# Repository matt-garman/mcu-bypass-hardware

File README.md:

<!-- SPDX-License-Identifier: CERN-OHL-P-2.0 -->

# MCU Hardware for Switch Debounce and Electric Instrument Effects Switching

## Overview

This is the companion repo to [mcu-bypass-firmware](https://github.com/matt-garman/mcu-bypass-firmware).

These hardware designs are intended to be used for electric
instrument effects (e.g. guitar effect pedals) bypass switching.
Many of these schemes rely on a microcontroller to act as the
"brains" of the switching scheme; see the other repo for MCU
firmware.

## License

Copyright (c) 2026 Matthew Garman

These hardware designs (schematics, PCB layouts, fabrication files,
documentation, and supporting scripts) are licensed under the
[CERN Open Hardware Licence Version 2 - Permissive](LICENSE)
(SPDX: `CERN-OHL-P-2.0`). The companion firmware is licensed separately
under the MIT License; see that repo for details.

In short, you may use, modify, and share these designs, and make and
sell products based on them, including commercial products. The main
condition is keeping the copyright and license notices available to
whoever receives the design files or a product built from them. The
designs are provided as-is, WITHOUT ANY WARRANTY; see the
[license](LICENSE) for the actual terms.

## Credit (appreciated, not required)

If you use these designs or the firmware in something you build, and
especially in something you sell, a shout-out would be much appreciated.
A line in your manual, product page, or "About" screen is perfect.
For example:

> Bypass switching based on [mcu-bypass-hardware](https://github.com/matt-garman/mcu-bypass-hardware)
> and [mcu-bypass-firmware](https://github.com/matt-garman/mcu-bypass-firmware)
> by Matt Garman.

You have my permission to use my name this way to credit these
projects. Please don't word it in a way that suggests I endorse, or
was involved with, your product.

## Projects

  - [projects/attiny13a-buffered-electrical-bypass-quasi-ic](projects/attiny13a-buffered-electrical-bypass-quasi-ic/)
  - [projects/attiny202-buffered-electrical-bypass-quasi-ic](projects/attiny202-buffered-electrical-bypass-quasi-ic/)
  - [projects/attiny13a-relay-bypass-quasi-ic](projects/attiny13a-relay-bypass-quasi-ic)

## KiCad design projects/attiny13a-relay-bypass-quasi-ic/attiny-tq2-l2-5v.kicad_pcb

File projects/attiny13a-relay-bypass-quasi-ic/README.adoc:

// SPDX-License-Identifier: CERN-OHL-P-2.0

= ATtiny13A Relay Bypass Module and Quasi-IC

== Overview

The design and intent of this module is broadly similar to that of
its sister projects,
link:../attiny13a-buffered-electrical-bypass-quasi-ic/[attiny13a-buffered-electrical-bypass-quasi-ic]
and
link:../attiny202-buffered-electrical-bypass-quasi-ic/[attiny202-buffered-electrical-bypass-quasi-ic].
Briefly, this
module is intended to offer the same "plug and play" convenience of
an integrated circuit, one that offers analog signal
switching, as well as engage/bypass state management
and status LED lighting/darking.

This module's key differences are:

  * This project uses through-hole components, and is therefore
    physically larger
  * While the project has "ATtiny13A" in the name, it actually uses
    any of three microcontrollers from the the "AVR Classic" family;
    specifically, firmware exists for ATtiny13A, ATtiny45, and
    ATtiny85 (the firmware is identical for all MCUs, except in
    necessary hardware-specific details)
  * Like the ATtiny13A-based Quasi-IC, this PCB uses a single row of
    pin headers; in fact the two modules are designed to be
    interchangeable
  * This module contains no buffers
  * This module uses a mechanical relay (Panasonic TQ-L2-5V) for
    true bypass switching
  * This module has additional I/O for use as a standalone module
    with commercial/off-the-shelf (COTS) PCBs (e.g. link:https://www.pedalpcb.com/[PedalPCB] 
    or link:https://www.aionfx.com/[AionFX] 
  * This is a "belt-and-suspenders" design (see below) that
    decouples the MCU from the relay coil via MOSFETs and protection
    diodes; thus, it can be easily adapted for use with other MCUs

== Design Notes

This is deliberately a "belt-and-suspenders" design.  That is, some
may argue that the design is over-engineered with some extraneous
parts.  Specifically: the use of the relay coil flyback protection
diodes (D1, D3), and the coil-current-sinking MOSFETs (Q1, Q3).  In
similar designs, the AVR MCU directly drives the relay coil,
removing the need for the protection diodes and current-sinking
transistors.  The AVR Classic MCU GPIO pins have built-in protection
diodes _and_ are rated to source/sink the relay coil current.
Similarly, it is also possible for the MCU to directly drive the
status LED.

Using the MOSFETs and protection diodes to isolate the relay coil
from the MCU provides additional safety for the MCU, though at the
expense of added PCB footpring and BOM cost.  Additionally, it makes
the design trivially adaptable to other microcontrollers which may
not have GPIO pins that are as rugged as the AVR Classic.  (MOSFET
gates present virtually zero load, so can be trivially activated by
practically any logic chip.)

_Presumably_, cheaper NPN BJT transistors (such as 2n3904) can be
used in place of the 2n7000 N-Channel MOSFETs.  *But this is
untested*.

While generally we refer to the TQ-L2-5V part for the relay, the
*TQ-L2-4.5V* is arguably the ideal part.  There is a voltage drop of
approximately 0.7V across the MOSFETs when they are switched on.
Therefore, the actual voltage presented to the relay coils is
approximately 4.3V, rather than 5V.  Thus, the "4.5V" part is a
better fit.  However, in practice, the 4.5V part is less common and
generally more expensive.  Given that the operating margins of the
TQ2 parts are fairly generous, the 5V part still has sufficient
margin in this design and works reliably.  Choose the 4.5V part only
if it's available and the cost is the same as the 5V part.

== Schematic

link:attiny-tq2-l2-5v.pdf[Downloadable PDF]

image::attiny-tq2-l2-5v.svg[opts=inline]

== Module Pinout

This module has a total of 15 pins with 2.54mm pitch.  There is
essentially three groups of pin headers.  The overall numbering, as
viewed from the component side, is somewhat awkward: 10, 11, 1, 2,
3, 4, 5, 6, 7, 8, 9, 12, 13, 14, 15.

The awkward numbering is so that the middle group of pins, i.e. 1
through 9, are compatible with the other quasi-IC modules that only
have these pins.

The other two groups of pins (10,11) and (12,13,14,15) allow the
module to be used generically with COTS PCBs.

....
 10| 11     1 | 2 | 3 | 4 | 5 | 6 | 7 | 8 | 9      12| 13| 14| 15
GND|VDC    +9V|GND|JIN|SND|LSW|RET|JOU|GND|FSW    GND|GND|LSW|+5V
....

[cols="1,2,6",options="header"]
|===
| Pin | Signal | Description

| 10, 2, 8, 12, 13
| GND
| Ground (0-volt)

| 11
| VDC
| Post-reverse polarity projection supply voltage; this is the
voltage that is created from the +9V pin, _after_ D2 and R13; this
can be used to power an effect PCB, particularly for many from AionFX 

| 1
| +9V
| Supply input; the module has a reverse-polarity shunt diode (D2)
and a 100-ohm series resistor (R13) on this pin

| 3
| JIN
| Signal input, from the input jack; routed directly to the relay

| 4
| SND
| Signal to the effect circuit's input, either JIN or GND; switched
by the relay

| 5, 14
| LSW
| Status LED cathode, switched to ground by Q3 through CLR1 (a
current-limiting resistor)

| 6
| RET
| The effect circuit's output, returning to the module; routed
directly to the relay

| 7
| JACK_OUT
| Signal output, either JIN or RET; routed directly to and switched
by the relay

| 9
| FSW
| One pin of a two-pin momentary, normally-open footswitch; the
pull-up and RC filter are on the module (the footswitch's other pin
is tied to GND)

| 15
| +5V
| The +5V supply used by the AVR MCU and the relay itself; this pin,
along with the LSW pin, can be used for the status LED (note that
generally a smaller current-limiting resistor can be used with 5V
versus 9V)
|===

// TODO: supply voltage range and typical current draw.

== Modifying

The KiCad project is
link:attiny-tq2-l2-5v.kicad_pro[attiny-tq2-l2-5v.kicad_pro],
in this directory.  KiCad version 10.0.5 was used.

== Fabrication and Assembly

The following files are offered for fabrication.  Caveats,
disclaimers and warnings:

  * I used these with link:JLCPCB[https://www.jlcpcb.com]; their
    suitability for other fabricators is unknown
  * They were generated from the KiCad project via
    link:kicad-jlcpcb-tools[https://github.com/bouni/kicad-jlcpcb-tools]

The files:

  * link:GERBER-attiny-tq2-l2-5v.zip[GERBER-attiny-tq2-l2-5v.zip]:
    Gerber files
  * link:attiny-tq2-l2-5v.BOM.csv[attiny-tq2-l2-5v.BOM.csv]: BOM (CSV format)
  * link:attiny-tq2-l2-5v.BOM.pdf[attiny-tq2-l2-5v.BOM.pdf]: BOM (PDF format)

== Build Reports

  * link:https://forum.pedalpcb.com/threads/pez-rojo-custom-menatone-red-snapper.30439/[Pez Rojo]
    (originally used the ATtiny202 quasi-IC, but later changed to this module)

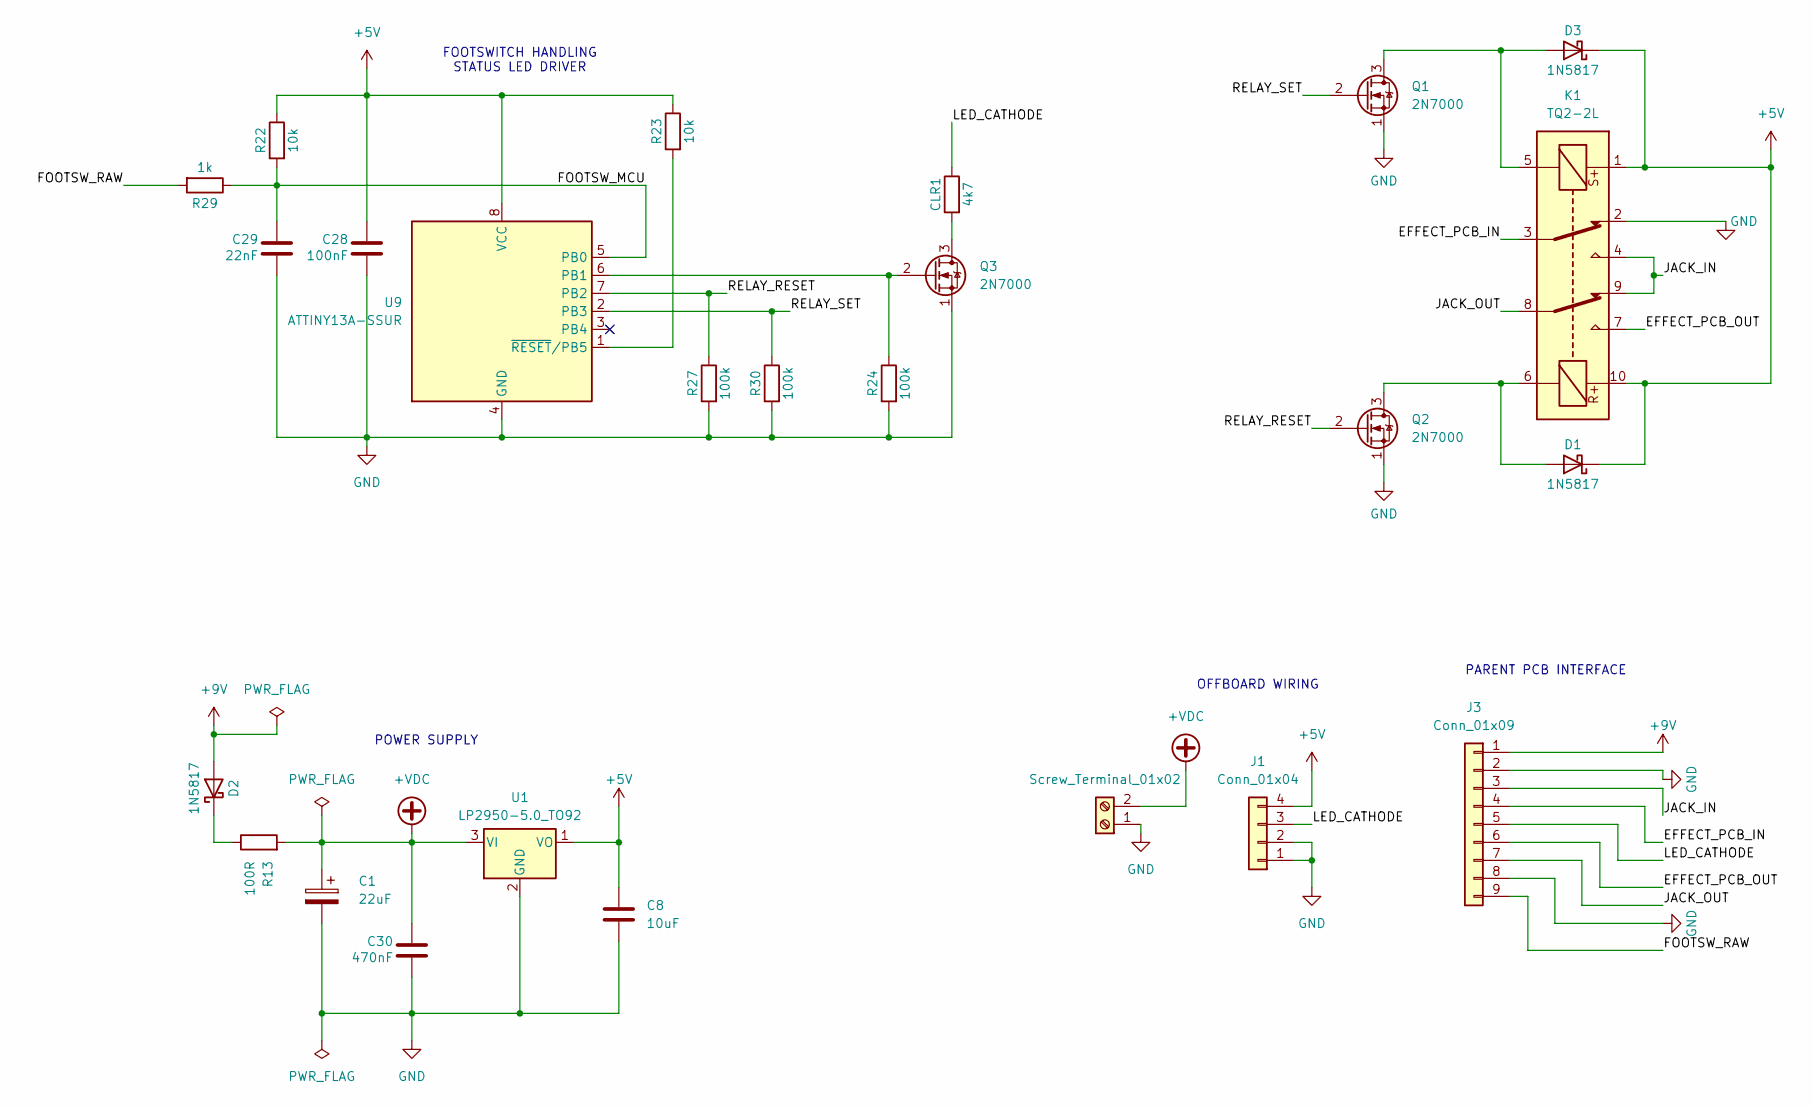
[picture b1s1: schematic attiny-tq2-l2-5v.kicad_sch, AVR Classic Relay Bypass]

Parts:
C1: 22uF; CP_Radial_D5.0mm_P2.50mm
C8: 10uF; C_Rect_L7.2mm_W2.5mm_P5.00mm_FKS2_FKP2_MKS2_MKP2; LCSC C13585
C28: 100nF; C_Rect_L7.2mm_W2.5mm_P5.00mm_FKS2_FKP2_MKS2_MKP2; LCSC C14663
C29: 22nF; C_Rect_L7.2mm_W2.5mm_P5.00mm_FKS2_FKP2_MKS2_MKP2; LCSC C21122
C30: 470nF; C_Rect_L7.2mm_W2.5mm_P5.00mm_FKS2_FKP2_MKS2_MKP2; LCSC C14663
CLR1: 4k7; R_Axial_DIN0204_L3.6mm_D1.6mm_P5.08mm_Horizontal; LCSC C23162
D1, D2, D3: 1N5817; D_DO-35_SOD27_P7.62mm_Horizontal
J1: Conn_01x04; OffboardWireHoles_1x04_P2.54mm
J3: Conn_01x09; OffboardWireHoles_1x09_P2.54mm
J8: Screw_Terminal_01x02; OffboardWireHoles_1x02_P2.54mm
K1: TQ2-2L; Relay_DPDT_A-4.5W-K
Q1, Q2, Q3: 2N7000; TO-92_Inline_Wide
R13: 100R; R_Axial_DIN0204_L3.6mm_D1.6mm_P5.08mm_Horizontal
R22: 10k; R_Axial_DIN0204_L3.6mm_D1.6mm_P5.08mm_Horizontal
R23: 10k; R_Axial_DIN0204_L3.6mm_D1.6mm_P5.08mm_Horizontal; LCSC C25804
R24, R27, R30: 100k; R_Axial_DIN0204_L3.6mm_D1.6mm_P5.08mm_Horizontal; LCSC C25803
R29: 1k; R_Axial_DIN0204_L3.6mm_D1.6mm_P5.08mm_Horizontal; LCSC C21190
U1: LP2950-5.0_TO92; TO-92_Inline_Wide
U9: ATTINY13A-SSUR; DIP-8_W7.62mm; LCSC C40382

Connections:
+5V: C8.2, C28.2, D1.1 (K), D3.1 (K), J1.4, K1.1, K1.10, R22.1, R23.1, U1.1 (VO), U9.8 (VCC)
+9V: D2.2 (A), J3.1
+VDC: C1.1, C30.2, J8.2, R13.2, U1.3 (VI)
/EFFECT_PCB_IN: J3.4, K1.3
/EFFECT_PCB_OUT: J3.6, K1.7
/FOOTSW_MCU: C29.2, R22.2, R29.1, U9.5 (PB0)
/FOOTSW_RAW: J3.9, R29.2
/JACK_IN: J3.3, K1.4, K1.9
/JACK_OUT: J3.7, K1.8
/LED_CATHODE: CLR1.1, J1.3, J3.5
/RELAY_RESET: Q2.2 (G), R27.1, U9.7 (PB2)
/RELAY_SET: Q1.2 (G), R30.1, U9.2 (PB3)
GND: C1.2, C8.1, C28.1, C29.1, C30.1, J1.1, J1.2, J3.2, J3.8, J8.1, K1.2, Q1.1 (S), Q2.1 (S), Q3.1 (S), R24.2, R27.2, R30.2, U1.2 (GND), U9.4 (GND)
unnamed: D1.2 (A), K1.6, Q2.3 (D)
unnamed: D2.1 (K), R13.1
unnamed: D3.2 (A), K1.5, Q1.3 (D)
unnamed: CLR1.2, Q3.3 (D)
unnamed: Q3.2 (G), R24.1, U9.6 (PB1)
unnamed: R23.2, U9.1 (~RESET/PB5)

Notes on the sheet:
PARENT PCB INTERFACE
FOOTSWITCH HANDLING STATUS LED DRIVER
OFFBOARD WIRING
POWER SUPPLY

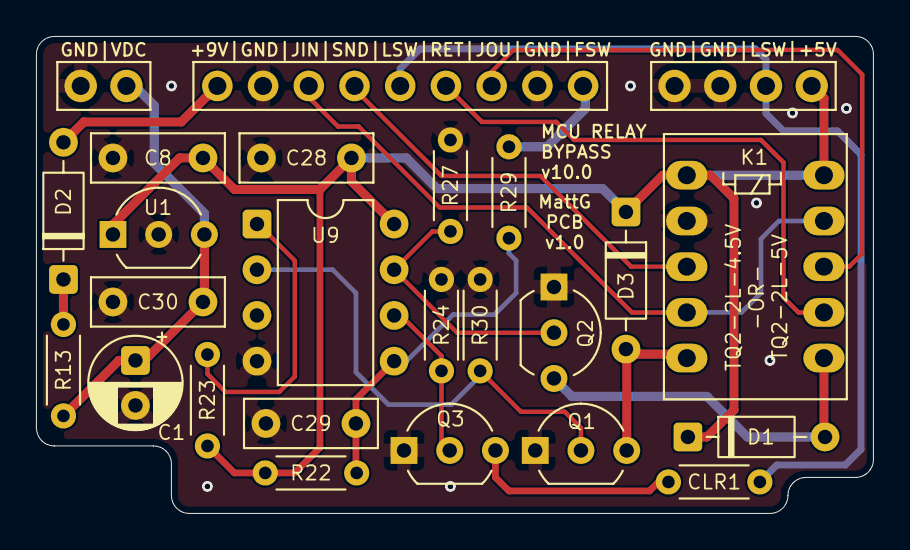
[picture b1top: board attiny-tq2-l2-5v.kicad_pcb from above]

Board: 2 copper layers, 46.5 x 26.5 mm, 25 parts (0 on the bottom side), 19 nets.

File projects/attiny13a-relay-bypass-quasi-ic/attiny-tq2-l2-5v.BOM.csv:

,,,
MCU Relay Bypass Module (True Bypass),,,
MCU Firmware: https://github.com/matt-garman/mcu-bypass-firmware,,,
,,,
,,,
Reference,Value,Footprint,Notes
R13,100R,DIN0204 / 3.6 x 1.6 x 5.08 mm,Forms PSU filter with C1
R29,1k,DIN0204 / 3.6 x 1.6 x 5.08 mm,Footswitch RC filter with C29
CLR1,4k7,DIN0204 / 3.6 x 1.6 x 5.08 mm,"Current-limiting resistor, adjust to taste"
R22,10k,DIN0204 / 3.6 x 1.6 x 5.08 mm,MCU footswitch pin pullup resistor
R23,10k,DIN0204 / 3.6 x 1.6 x 5.08 mm,MCU reset pin pullup resistor
R24,100k,DIN0204 / 3.6 x 1.6 x 5.08 mm,LED mosfet gate pulldown resistor
R27,100k,DIN0204 / 3.6 x 1.6 x 5.08 mm,Relay reset mosfet gate pulldown resistor
R30,100k,DIN0204 / 3.6 x 1.6 x 5.08 mm,Relay set mosfet gate pulldown resistor
,,,
C29,22nF,Box film cap 7.2 x 2.5 mm,Footswitch RC filter with R29
C28,100nF,Ceramic X7R or box film cap 7.2 x 2.5 mm,MCU supply decoupling
C30,470nF,Ceramic X7R or box film cap 7.2 x 2.5 mm,5v LDO supply decoupling/filtering
C8,10uF,Ceramic X7R 7.2 x 2.5 mm,5v bulk supply decoupling
C1,>=10uF,Ceramic X7R or Electrolytic 5mm diameter (low profile),Forms PSU filter with R13; bigger is better (as space allows)
,,,
D1,1N5817,DO-35,Relay coil flyback protection diode
D2,1N5817,DO-35,Reverse polarity protection
D3,1N5817,DO-35,Relay coil flyback protection diode
,,,
Q1,2N7000,TO-92,"other N-MOS ok, but mind pinout"
Q2,2N7000,TO-92,"other N-MOS ok, but mind pinout"
Q3,2N7000,TO-92,"other N-MOS ok, but mind pinout"
,,,
K1,TQ2-2L-5V,Panasonic TQ2-2L-5V or -4.5V relay,
U1,LP2950-5.0_TO92,TO-92,5v LDO; 78L05 ok but mind pinout
U9,ATtiny13A,DIP-8,"Can also use ATtiny45, ATtiny85"

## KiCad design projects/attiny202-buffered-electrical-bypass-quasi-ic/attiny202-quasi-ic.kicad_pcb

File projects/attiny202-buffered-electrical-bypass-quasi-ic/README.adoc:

// SPDX-License-Identifier: CERN-OHL-P-2.0

= ATtiny202 Buffered Electrical Bypass Quasi-IC

== Overview

See the sister project
link:../attiny13a-buffered-electrical-bypass-quasi-ic/[attiny13a-buffered-electrical-bypass-quasi-ic]
for a detailed discussion of this design.  The design intent and
functionality of the two modules are identical.  That is, this
module is intended to offer the same "plug and play" convenience of
an integrated circuit, one that offers analog signal
buffering and switching, as well as engage/bypass state management
and status LED lighting/darking.

The differences are:

  * This project uses the ATtiny202 microcontroller, whereas the
    other uses ATtiny13a.  The actual firmware behavior is the same;
    the source itself differs only in the obligatory
    hardware-specific details.
  * This PCB design is much smaller, with a 43x16mm footprint
  * This design is a 4-layer PCB, whereas the other is 2-layer
  * This PCB uses a single row of pin headers to enable _vertical_
    mounting (i.e. perpendicular to the parent PCB) using
    right-angle pin headers (credit to
    link:https://www.diystompboxes.com/smfforum/index.php?msg=1312371[RG Keen for the suggestion])

== Schematic

link:attiny202-quasi-ic.pdf[Downloadable PDF]

image::attiny202-quasi-ic.svg[opts=inline]

== Module Pinout

The module plugs into its parent PCB through a single row of nine
pins, 2.54 mm pitch.  The pins are numbered 1 through 9,
left-to-right, as viewed from the component side.

....
   1 | 2 | 3 | 4 | 5 | 6 | 7 | 8 | 9
  VDC|GND|JIN|SND|LSW|RET|JOU|GND|FSW
....

[cols="1,2,6",options="header"]
|===
| Pin | Signal | Description

| 1
| VDC
| Supply input; the module has a reverse-polarity shunt diode (D2)
and a 22-ohm series resistor (R5) on this pin

| 2, 8
| GND
| Ground (0-volt)

| 3
| JIN
| Signal input, from the input jack; goes to the input buffer

| 4
| SND
| Buffered signal to the effect circuit's input, switched by the
TMUX4053 and AC-coupled (C10)

| 5
| LSW
| Status LED cathode, switched to ground by Q3 through a 4.7k-ohm
resistor (R26) on the module.  Connect the LED's anode to the supply;
the parent PCB _may_ need additional current-limiting resistance,
depending on desired LED brightness and/or LED type (I typically add
an additional 3.3k-ohm for ultrabright/high-efficiency LEDs)

| 6
| RET
| The effect circuit's output, returning to the module; AC-coupled
(C9)

| 7
| JACK_OUT
| Buffered signal output, to the output jack

| 9
| FSW
| Momentary, normally-open footswitch to ground; the pull-up, ferrite
bead, RC filter and ESD protection are on the module
|===

// TODO: supply voltage range and typical current draw.

== Modifying

The KiCad project is
link:attiny202-quasi-ic.kicad_pro[attiny202-quasi-ic.kicad_pro],
in this directory.  KiCad version 10.0.5 was used.

== Fabrication and Assembly

The following files are offered for fabrication.  Caveats,
disclaimers and warnings:

  * I used these with link:JLCPCB[https://www.jlcpcb.com]; their
    suitability for other fabricators is unknown
  * They were generated from the KiCad project via
    link:kicad-jlcpcb-tools[https://github.com/bouni/kicad-jlcpcb-tools]
  * The files were generated on *August 29, 2026*; JLC/LCSC part
    numbers were valid at that time, but are subject to change
  * *_Some parts' orientation in the CPL file is incorrect_*; I had
    to manually fix the orientation of most polarized parts and ICs
    using JLC's web interface
  * This module was designed for automated assembly; successful
    hand-soldering is effectively impossible

The files:

  * link:BOM-attiny202-quasi-ic.csv[BOM-attiny202-quasi-ic.csv]:
    Bill of Materials with LCSC part numbers
  * link:CPL-attiny202-quasi-ic.csv[CPL-attiny202-quasi-ic.csv]:
    Component Placement List (_see warning above_)
  * link:GERBER-attiny202-quasi-ic.zip[GERBER-attiny202-quasi-ic.zip]:
    Gerber files

== Build Reports

  * link:https://forum.pedalpcb.com/threads/nashville-nobility-custom-nobels-odr-1bc.30339/[Nashville Nobility]
  * link:https://forum.pedalpcb.com/threads/the-enchanter-custom-timmy-jan-ray.30400/[The Enchanter]
  * link:https://forum.pedalpcb.com/threads/carbon-squish-custom-diamond-compressor.30616/[Carbon Squish]
  * link:https://forum.pedalpcb.com/threads/pez-rojo-custom-menatone-red-snapper.30439/[Pez Rojo]

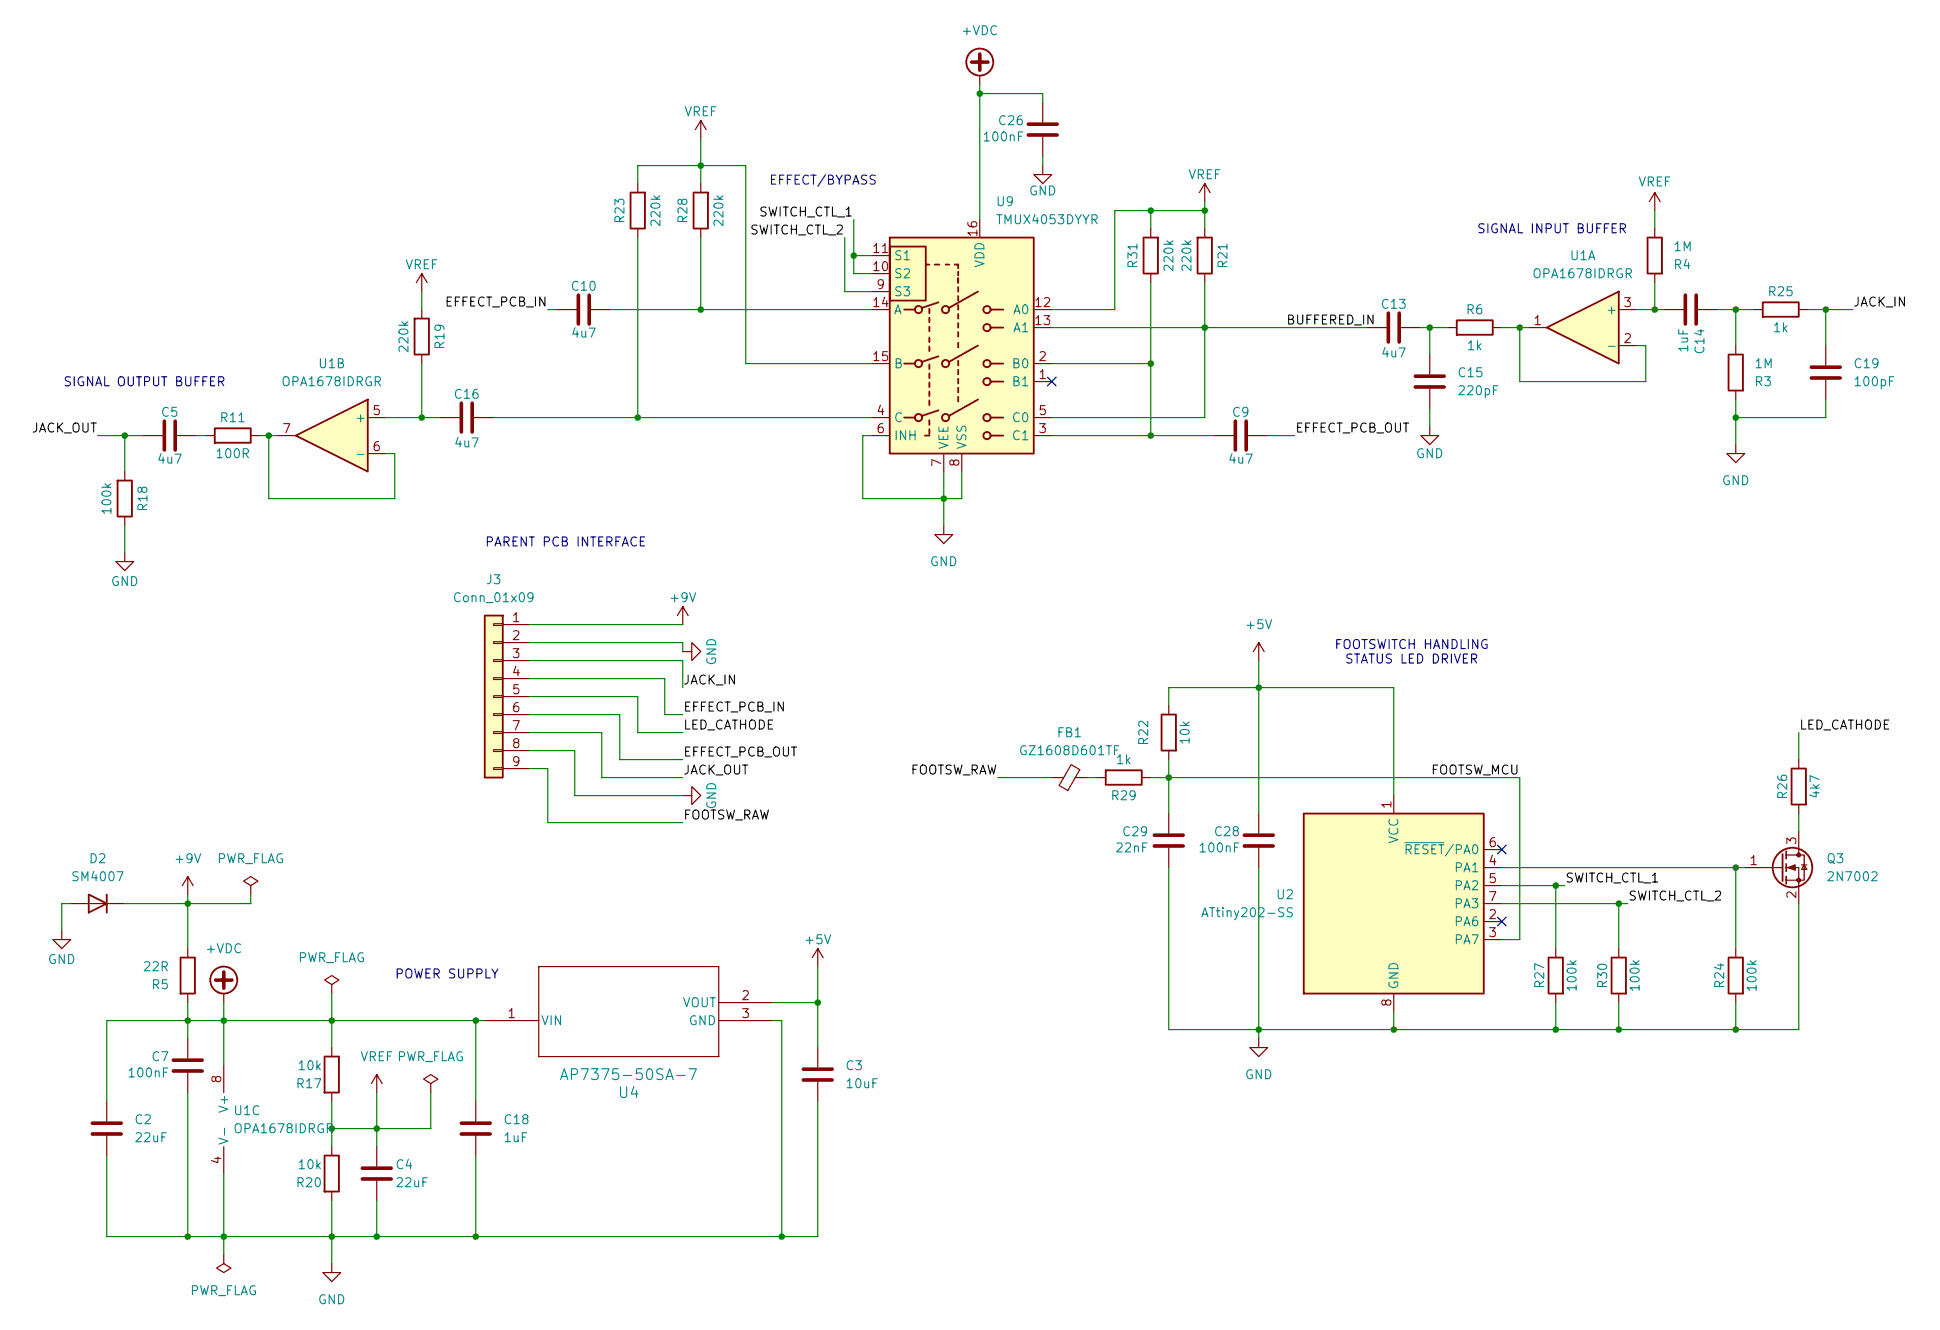
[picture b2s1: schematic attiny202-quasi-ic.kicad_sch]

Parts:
C2, C4: 22uF; C_1206_3216Metric; LCSC C12891
C3: 10uF; C_1206_3216Metric; LCSC C13585
C5, C9, C10, C13, C16: 4u7; C_1206_3216Metric; LCSC C29823
C7, C26, C28: 100nF; C_0603_1608Metric; LCSC C14663
C14, C18: 1uF; C_0805_2012Metric; LCSC C28323
C15: 220pF; C_0603_1608Metric; LCSC C1603
C19: 100pF; C_0603_1608Metric; LCSC C14858
C29: 22nF; C_0603_1608Metric; LCSC C21122
D2: SM4007; D_SOD-123F; LCSC C64898
FB1: GZ1608D601TF; L_0603_1608Metric; LCSC C1002
J3: Conn_01x09; OffboardWireHoles_1x09_P2.54mm
Q3: 2N7002; SOT-23; LCSC C8545
R3, R4: 1M; R_0603_1608Metric; LCSC C22935
R5: 22R; R_1206_3216Metric; LCSC C17958
R6, R25, R29: 1k; R_0603_1608Metric; LCSC C21190
R11: 100R; R_0603_1608Metric; LCSC C22775
R17, R20, R22: 10k; R_0603_1608Metric; LCSC C25804
R18, R24, R27, R30: 100k; R_0603_1608Metric; LCSC C25803
R19, R21, R23, R28, R31: 220k; R_0603_1608Metric; LCSC C22961
R26: 4k7; R_0603_1608Metric; LCSC C23162
U1: OPA1678IDRGR; WSON-8-1EP_3x3mm_P0.5mm_EP1.2x2mm; LCSC C2861885
U2: ATtiny202-SS; SOIC-8_3.9x4.9mm_P1.27mm; LCSC C2052951
U4: AP7375-50SA-7; SOT23_DIO; LCSC C6500991
U9: TMUX4053DYYR; Texas_DYY0016A_TSOT-23-16_2x4.2mm_P0.5mm; LCSC C22388988

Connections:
+5V: C3.2, C28.2, R22.1, U2.1 (VCC), U4.2 (VOUT)
+9V: D2.1 (K), J3.1, R5.1
+VDC: C2.2, C7.2, C18.2, C26.2, R5.2, R17.1, U1.8 (V+), U4.1 (VIN), U9.16 (VDD)
/BUFFERED_IN: C13.2, R21.1, U9.5 (C0), U9.13 (A1)
/EFFECT_PCB_IN: C10.1, J3.4
/EFFECT_PCB_OUT: C9.2, J3.6
/FOOTSW_MCU: C29.2, R22.2, R29.1, U2.3 (PA7)
/FOOTSW_RAW: FB1.1, J3.9
/JACK_IN: C19.2, J3.3, R25.1
/JACK_OUT: C5.2, J3.7, R18.2
/LED_CATHODE: J3.5, R26.1
/SWITCH_CTL_1: R27.1, U2.5 (PA2), U9.10 (S2), U9.11 (S1)
/SWITCH_CTL_2: R30.1, U2.7 (PA3), U9.9 (S3)
GND: C2.1, C3.1, C4.1, C7.1, C15.1, C18.1, C19.1, C26.1, C28.1, C29.1, D2.2 (A), J3.2, J3.8, Q3.2 (S), R3.2, R18.1, R20.2, R24.2, R27.2, R30.2, U1.4 (V-), U2.8 (GND), U4.3 (GND), U9.6 (INH), U9.7 (VEE), U9.8 (VSS)
unnamed: C5.1, R11.2
unnamed: C13.1, C15.2, R6.2
unnamed: C14.2, R3.1, R25.2
unnamed: FB1.2, R29.2
unnamed: Q3.3 (D), R26.2
unnamed: Q3.1 (G), R24.1, U2.4 (PA1)
unnamed: C14.1, R4.2, U1.3 (+)
unnamed: R6.1, U1.1, U1.2 (-)
unnamed: C16.2, R19.1, U1.5 (+)
unnamed: R11.1, U1.6 (-), U1.7
unnamed: C10.2, R28.1, U9.14 (A)
unnamed: C9.1, R31.1, U9.2 (B0), U9.3 (C1)
unnamed: C16.1, R23.1, U9.4 (C)
VREF: C4.2, R4.1, R17.2, R19.2, R20.1, R21.2, R23.2, R28.2, R31.2, U9.12 (A0), U9.15 (B)

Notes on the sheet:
PARENT PCB INTERFACE
SIGNAL INPUT BUFFER
EFFECT/BYPASS
FOOTSWITCH HANDLING STATUS LED DRIVER
SIGNAL OUTPUT BUFFER
POWER SUPPLY

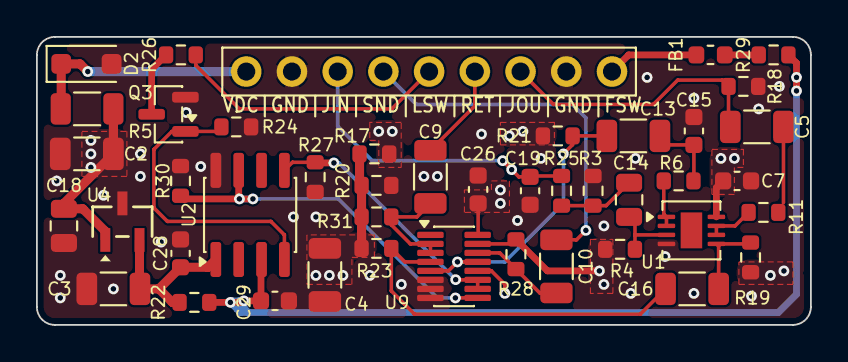
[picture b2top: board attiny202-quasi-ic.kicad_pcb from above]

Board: 4 copper layers, 43.0 x 16.0 mm, 44 parts (0 on the bottom side), 28 nets.

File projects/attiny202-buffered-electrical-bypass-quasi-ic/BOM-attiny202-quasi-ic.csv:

Comment,Designator,Footprint,LCSC,Quantity
100R,R11,R_0603_1608Metric,C22775,1
100k,"R18,R24,R27,R30",R_0603_1608Metric,C25803,4
100nF,"C26,C28,C7",C_0603_1608Metric,C14663,3
100pF,C19,C_0603_1608Metric,C14858,1
10k,"R17,R20,R22",R_0603_1608Metric,C25804,3
10uF,C3,C_1206_3216Metric,C13585,1
1M,"R3,R4",R_0603_1608Metric,C22935,2
1k,"R25,R29,R6",R_0603_1608Metric,C21190,3
1uF,"C14,C18",C_0805_2012Metric,C28323,2
220k,"R19,R21,R23,R28,R31",R_0603_1608Metric,C22961,5
220pF,C15,C_0603_1608Metric,C1603,1
22R,R5,R_1206_3216Metric,C17958,1
22nF,C29,C_0603_1608Metric,C21122,1
22uF,"C2,C4",C_1206_3216Metric,C12891,2
2N7002,Q3,SOT-23,C8545,1
4k7,R26,R_0603_1608Metric,C23162,1
4u7,"C10,C13,C16,C5,C9",C_1206_3216Metric,C29823,5
AP7375-50SA-7,U4,SOT23_DIO,C6500991,1
ATtiny202-SS,U2,SOIC-8_3.9x4.9mm_P1.27mm,C2052951,1
GZ1608D601TF,FB1,L_0603_1608Metric,C1002,1
OPA1678IDRGR,U1,WSON-8-1EP_3x3mm_P0.5mm_EP1.2x2mm,C2861885,1
SM4007,D2,D_SOD-123F,C64898,1
TMUX4053DYYR,U9,Texas_DYY0016A_TSOT-23-16_2x4.2mm_P0.5mm,C22388988,1

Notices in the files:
projects/attiny13a-relay-bypass-quasi-ic/attiny-tq2-l2-5v.kicad_pcb:
© 2026 Matthew Garman
